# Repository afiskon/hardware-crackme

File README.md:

# hardware-crackme
Simple hardware crackme

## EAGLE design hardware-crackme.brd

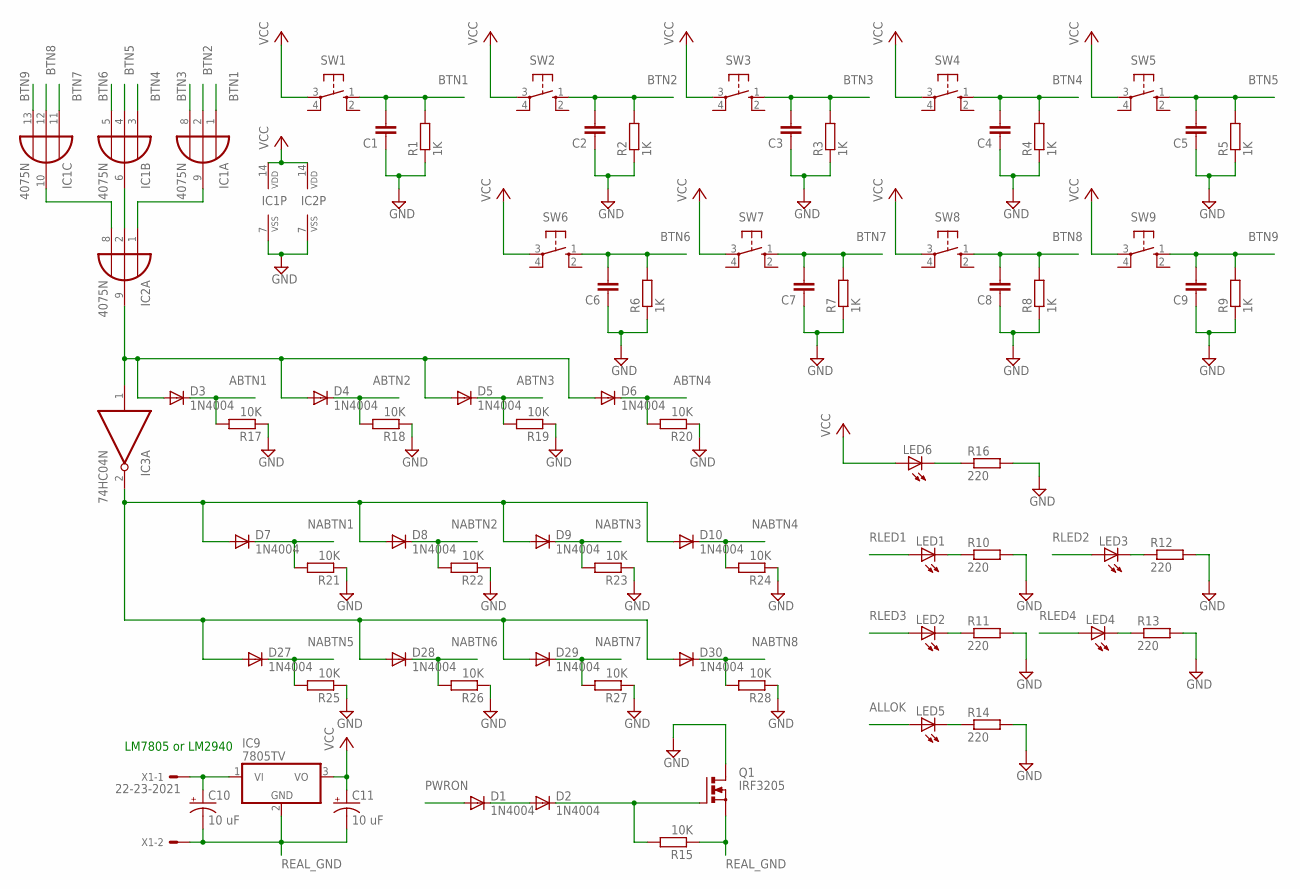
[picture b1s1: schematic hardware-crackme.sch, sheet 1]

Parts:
C1, C2, C3, C4, C5, C6, C7, C8, C9: C-EU050-025X075; C050-025X075
C10, C11: 10 uF; E2,5-7
D1, D2, D3, D4, D5, D6, D7, D8, D9, D10, D27, D28, D29, D30: 1N4004; DO41-10
IC1, IC2: 4075N; DIL14
IC3: 74HC04N; DIL14
IC9: 7805TV; TO220V
LED1, LED2, LED3, LED4, LED5, LED6: LED5MM
Q1: IRF3205; TO220BV
R1, R2, R3, R4, R5, R6, R7, R8, R9: 1K; 0207/7
R10, R11, R12, R13, R14, R16: 220; 0207/7
R15, R17, R18, R19, R20, R21, R22, R23, R24, R25, R26, R27, R28: 10K; 0207/7
SW1, SW2, SW3, SW4, SW5, SW6, SW7, SW8, SW9: 10-XX; B3F-10XX
X1: 22-23-2021

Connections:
ABTN1: D3.C, R17.2; also elsewhere on the board
ABTN2: D4.C, R18.2; also elsewhere on the board
ABTN3: D5.C, R19.2; also elsewhere on the board
ABTN4: D6.C, R20.2; also elsewhere on the board
ALLOK: LED5.A; also elsewhere on the board
BTN1: C1.2, IC1.1 (I0), R1.2, SW1.1 (S); also elsewhere on the board
BTN2: C2.2, IC1.2 (I1), R2.2, SW2.1 (S); also elsewhere on the board
BTN3: C3.2, IC1.8 (I2), R3.2, SW3.1 (S); also elsewhere on the board
BTN4: C4.2, IC1.3 (I0), R4.2, SW4.1 (S); also elsewhere on the board
BTN5: C5.2, IC1.4 (I1), R5.2, SW5.1 (S); also elsewhere on the board
BTN6: C6.2, IC1.5 (I2), R6.2, SW6.1 (S); also elsewhere on the board
BTN7: C7.2, IC1.11 (I0), R7.2, SW7.1 (S); also elsewhere on the board
BTN8: C8.2, IC1.12 (I1), R8.2, SW8.1 (S); also elsewhere on the board
BTN9: C9.2, IC1.13 (I2), R9.2, SW9.1 (S); also elsewhere on the board
GND: C1.1, C2.1, C3.1, C4.1, C5.1, C6.1, C7.1, C8.1, C9.1, IC1.7 (VSS), IC2.7 (VSS), IC3.7 (GND), Q1.D, R1.1, R2.1, R3.1, R4.1, R5.1, R6.1, R7.1, R8.1, R9.1, R10.2, R11.2, R12.2, R13.2, R14.2, R16.2, R17.1, R18.1, R19.1, R20.1, R21.1, R22.1, R23.1, R24.1, R25.1, R26.1, R27.1, R28.1; also elsewhere on the board
unnamed: C10.+, IC9.1 (VI), X1.1
unnamed: D2.C, Q1.G, R15.2
unnamed: LED1.K (C), R10.1
unnamed: D1.C, D2.A
unnamed: LED2.K (C), R11.1
unnamed: LED6.K (C), R16.1
unnamed: LED3.K (C), R12.1
unnamed: LED4.K (C), R13.1
unnamed: LED5.K (C), R14.1
unnamed: IC1.9 (O), IC2.1 (I0)
unnamed: IC1.6 (O), IC2.2 (I1)
unnamed: IC1.10 (O), IC2.8 (I2)
unnamed: D3.A, D4.A, D5.A, D6.A, IC2.9 (O), IC3.1 (I)
unnamed: D7.A, D8.A, D9.A, D10.A, D27.A, D28.A, D29.A, D30.A, IC3.2 (O)
NABTN1: D7.C, R21.2; also elsewhere on the board
NABTN2: D8.C, R22.2; also elsewhere on the board
NABTN3: D9.C, R23.2; also elsewhere on the board
NABTN4: D10.C, R24.2; also elsewhere on the board
NABTN5: D27.C, R25.2; also elsewhere on the board
NABTN6: D28.C, R26.2; also elsewhere on the board
NABTN7: D29.C, R27.2; also elsewhere on the board
NABTN8: D30.C, R28.2; also elsewhere on the board
PWRON: D1.A; also elsewhere on the board
REAL_GND: C10.-, C11.-, IC9.2 (GND), Q1.S, R15.1, X1.2
RLED1: LED1.A; also elsewhere on the board
RLED2: LED3.A; also elsewhere on the board
RLED3: LED2.A; also elsewhere on the board
RLED4: LED4.A; also elsewhere on the board
VCC: C11.+, IC1.14 (VDD), IC2.14 (VDD), IC3.14 (VCC), IC9.3 (VO), LED6.A, SW1.3, SW2.3, SW3.3, SW4.3, SW5.3, SW6.3, SW7.3, SW8.3, SW9.3; also elsewhere on the board

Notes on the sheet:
LM7805 or LM2940

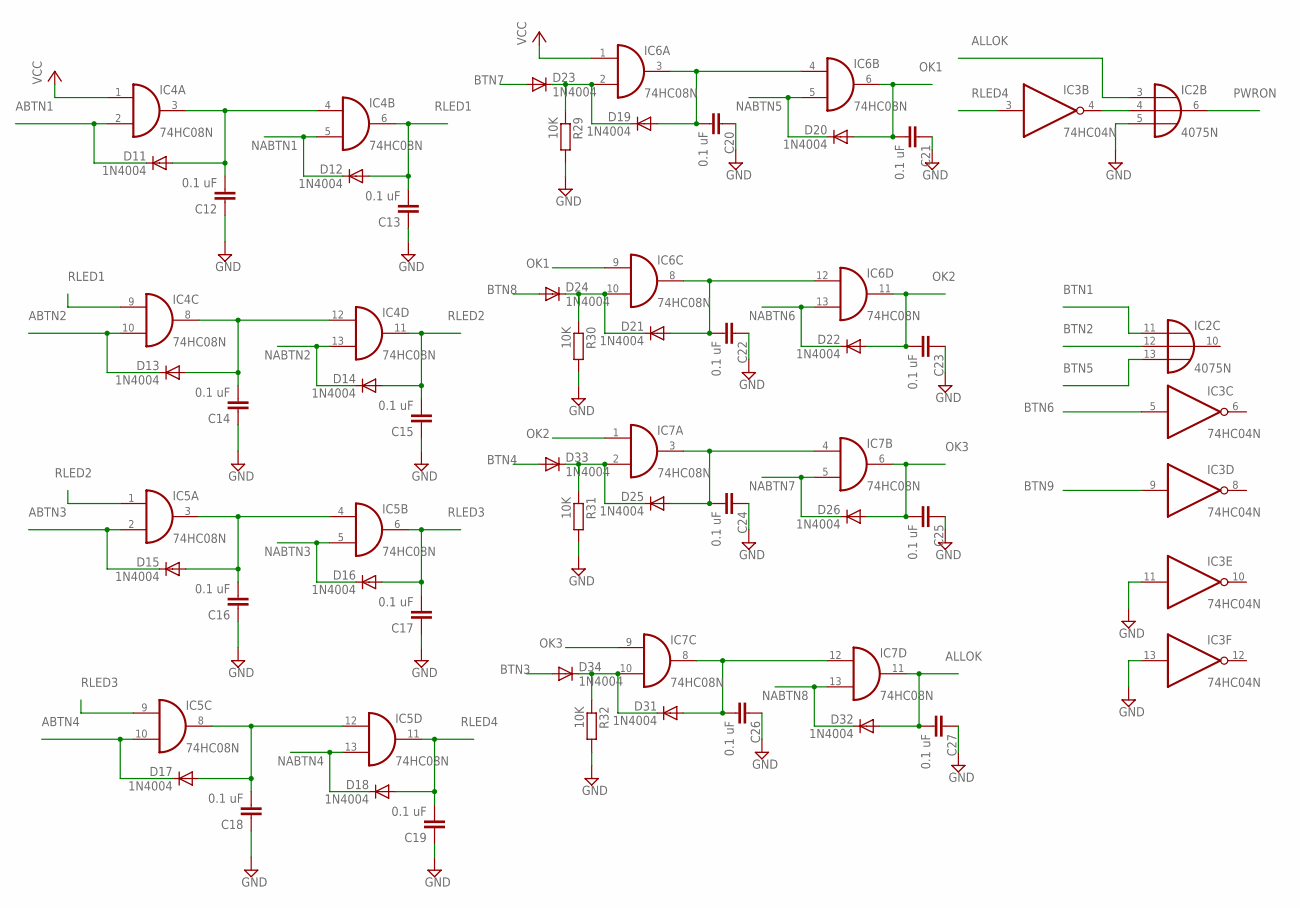
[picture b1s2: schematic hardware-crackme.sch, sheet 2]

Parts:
C12, C13, C14, C15, C16, C17, C18, C19, C20, C21, C22, C23, C24, C25, C26, C27: 0.1 uF; C050-025X075
D11, D12, D13, D14, D15, D16, D17, D18, D19, D20, D21, D22, D23, D24, D25, D26, D31, D32, D33, D34: 1N4004; DO41-10
IC2: 4075N; DIL14
IC3: 74HC04N; DIL14
IC4, IC5, IC6, IC7: 74HC08N; DIL14
R29, R30, R31, R32: 10K; 0207/7

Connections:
ABTN1: D11.C, IC4.2 (I1); also elsewhere on the board
ABTN2: D13.C, IC4.10 (I1); also elsewhere on the board
ABTN3: D15.C, IC5.2 (I1); also elsewhere on the board
ABTN4: D17.C, IC5.10 (I1); also elsewhere on the board
ALLOK: C27.2, D32.A, IC2.3 (I0), IC7.11 (O); also elsewhere on the board
BTN1: IC2.11 (I0); also elsewhere on the board
BTN2: IC2.12 (I1); also elsewhere on the board
BTN3: D34.A; also elsewhere on the board
BTN4: D33.A; also elsewhere on the board
BTN5: IC2.13 (I2); also elsewhere on the board
BTN6: IC3.5 (I); also elsewhere on the board
BTN7: D23.A; also elsewhere on the board
BTN8: D24.A; also elsewhere on the board
BTN9: IC3.9 (I); also elsewhere on the board
GND: C12.1, C13.1, C14.1, C15.1, C16.1, C17.1, C18.1, C19.1, C20.1, C21.1, C22.1, C23.1, C24.1, C25.1, C26.1, C27.1, IC2.5 (I2), IC3.7 (GND), IC3.11 (I), IC3.13 (I), IC4.7 (GND), IC5.7 (GND), IC6.7 (GND), IC7.7 (GND), R29.2, R30.2, R31.2, R32.2; also elsewhere on the board
unnamed: C12.2, D11.A, IC4.3 (O), IC4.4 (I0)
unnamed: C14.2, D13.A, IC4.8 (O), IC4.12 (I0)
unnamed: IC2.4 (I1), IC3.4 (O)
unnamed: C16.2, D15.A, IC5.3 (O), IC5.4 (I0)
unnamed: C18.2, D17.A, IC5.8 (O), IC5.12 (I0)
unnamed: C20.2, D19.A, IC6.3 (O), IC6.4 (I0)
unnamed: C22.2, D21.A, IC6.8 (O), IC6.12 (I0)
unnamed: D21.C, D24.C, IC6.10 (I1), R30.1
unnamed: D19.C, D23.C, IC6.2 (I1), R29.1
unnamed: C24.2, D25.A, IC7.3 (O), IC7.4 (I0)
unnamed: C26.2, D31.A, IC7.8 (O), IC7.12 (I0)
unnamed: D31.C, D34.C, IC7.10 (I1), R32.1
unnamed: D25.C, D33.C, IC7.2 (I1), R31.1
NABTN1: D12.C, IC4.5 (I1); also elsewhere on the board
NABTN2: D14.C, IC4.13 (I1); also elsewhere on the board
NABTN3: D16.C, IC5.5 (I1); also elsewhere on the board
NABTN4: D18.C, IC5.13 (I1); also elsewhere on the board
NABTN5: D20.C, IC6.5 (I1); also elsewhere on the board
NABTN6: D22.C, IC6.13 (I1); also elsewhere on the board
NABTN7: D26.C, IC7.5 (I1); also elsewhere on the board
NABTN8: D32.C, IC7.13 (I1); also elsewhere on the board
OK1: C21.2, D20.A, IC6.6 (O), IC6.9 (I0)
OK2: C23.2, D22.A, IC6.11 (O), IC7.1 (I0)
OK3: C25.2, D26.A, IC7.6 (O), IC7.9 (I0)
PWRON: IC2.6 (O); also elsewhere on the board
RLED1: C13.2, D12.A, IC4.6 (O), IC4.9 (I0); also elsewhere on the board
RLED2: C15.2, D14.A, IC4.11 (O), IC5.1 (I0); also elsewhere on the board
RLED3: C17.2, D16.A, IC5.6 (O), IC5.9 (I0); also elsewhere on the board
RLED4: C19.2, D18.A, IC3.3 (I), IC5.11 (O); also elsewhere on the board
VCC: IC3.14 (VCC), IC4.1 (I0), IC4.14 (VCC), IC5.14 (VCC), IC6.1 (I0), IC6.14 (VCC), IC7.14 (VCC); also elsewhere on the board

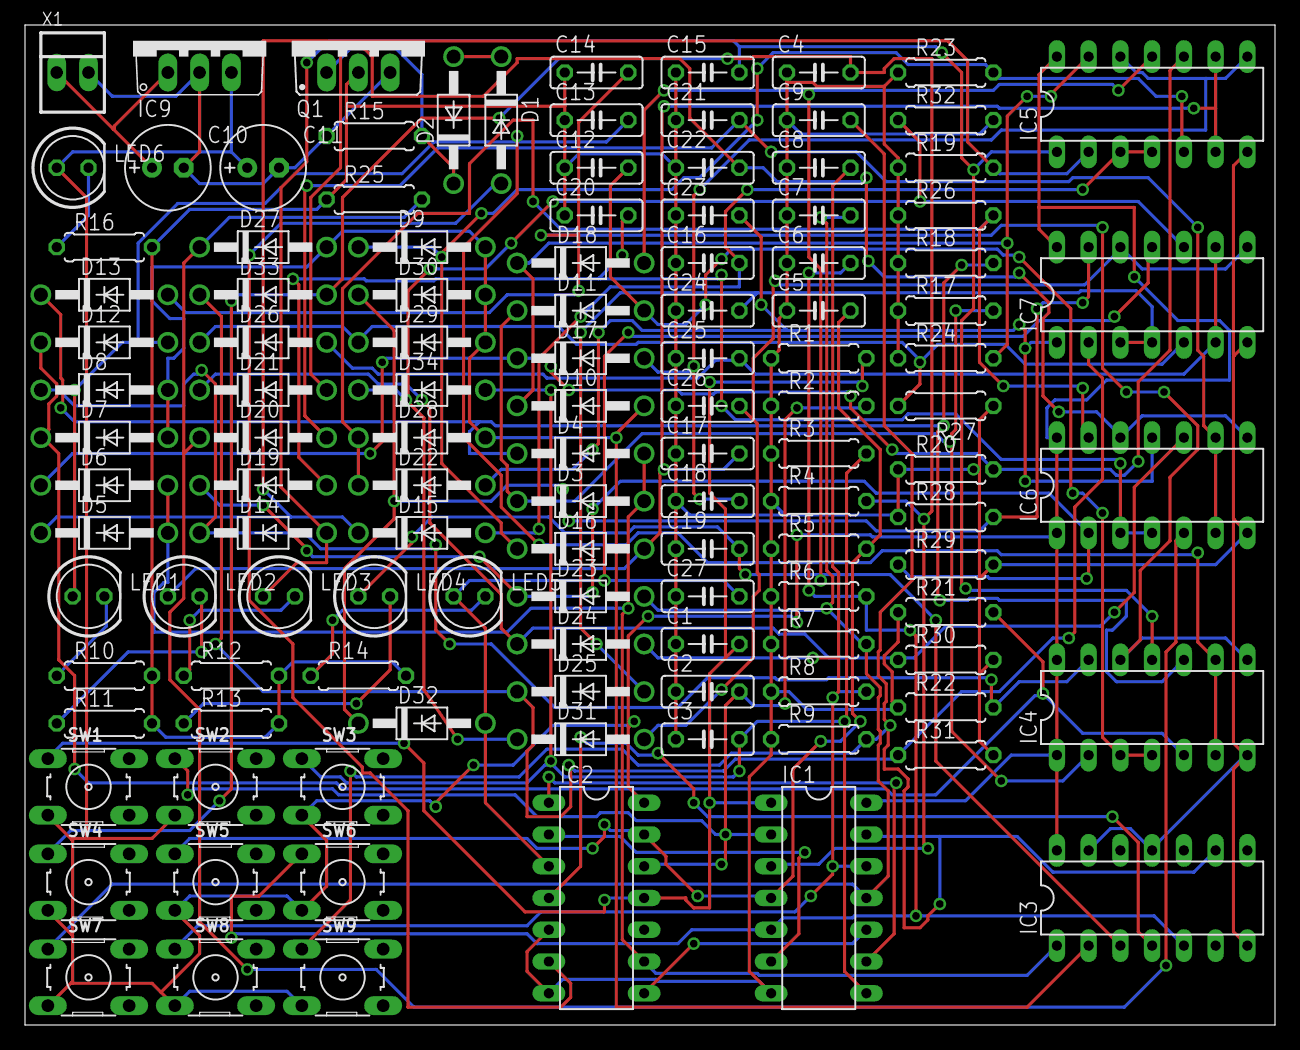
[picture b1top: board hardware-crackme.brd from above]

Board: 2 copper layers, 100.0 x 80.0 mm, 118 parts (0 on the bottom side), 60 nets.

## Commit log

2017-08-28 Moved from a sandbox repository
2017-08-28 PDF files added
